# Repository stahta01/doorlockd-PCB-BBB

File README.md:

# doorlockd-PCB-BBB

Kicad drawing for doorlockd electronics on a Beagleboard black cape.

### component list
|Ref| |Value|
| --- | --- | --- |
|C1|C|1uF |
|C2|C|1uF|
|C3|CP|470u|
|D1|LED|LED|
|D2|1N4007|1N4007|
|D3|LED|LED|
|D4|1N4007|1N4007|
|J1|Conn_01x02|LED 1|
|J10|Conn_01x03|Duo LED|
|J11|Barrel_Jack_Switch|Barrel_Jack_Switch|
|J12|Conn_01x08|RFID RC522|
|J13|Conn_01x02|Solenoid 12V|
|J14|Conn_01x02|jumper|
|J2|Conn_01x02|Button 2|
|J3|Conn_01x02|LED 2|
|J4|Conn_01x02|Button 1|
|J5|Conn_01x02|Buzzer 12V|
|P8|Conn_02x23_Odd_Even|BeagleBone_Black_Header|
|P9|Conn_02x23_Odd_Even|BeagleBone_Black_Header|
|Q1|Q_NMOS_GDS|STU60N3LH5|
|Q2|Q_NMOS_GDS|STU60N3LH5|
|R1|R|Ω LED1 |
|R14|R|Ω DuoLED|
|R15|R|Ω DuoLED|
|R16|R|100|
|R17|R|2k2|
|R2|R|pull_up|
|R3|R|220|
|R4|R|Ω LED2|
|R5|R|pull_up|
|R6|R|220|
|R7|R|100|
|R8|R|2k2|
|U1|TSR_1-2450|TSR_1-2450|

#### LED resistor notes
Choose the resistors based on the LEDs you use.

|Led |resistors|
| --- | ---: |
|red | 100 ohm|
|green | 60 ohm|
|yellow | 48 ohm|
|blue |4 ohm|

### connected IO ports
| |port|chip,line<sup>\*1</sup>|name|
| --- | --- | --- | --- |
|IO|P8_17|gpiochip0 27|Button1|
|IO|P9_12|gpiochip1 28|Solenoid|
|IO|P9_14|gpiochip1 18|UILED1|
|IO|P8_18|gpiochip2 1|Button2|
|IO|P9_17|gpiochip0 5|RC522_SDA|
|IO|P9_22|gpiochip0 2|RC522_SCK|
|IO|P9_18|gpiochip0 4|RC522_MOSI|
|IO|P9_21|gpiochip0 3|RC522_MISO|
|IO|P9_15|gpiochip1 16|RC522_IRQ|
|IO|P9_23|gpiochip1 17|RC522_RST|
|IO|P8_13|gpiochip0 23|UI_DuoLED1r|
|IO|P8_19|gpiochip0 22|UI_DuoLED1g|
|IO|P9_16|gpiochip1 19|UILED2|
|IO|P8_9|gpiochip2 5|Buzzer|

<sub>*\*1):* GPIO Chip+line for gpiod, reference taken from https://elinux.org/Beagleboard:BeagleBone_cape_interface_spec </sub>

### Connecting PN532 board
This board was originally designed for use with the RC522 NFC reader,
but is also usable with the PN532 reader (which has better range and
reliability).

 - BBB SCK pin (`RC522_SCK`) is `UART2_RXD` -> connect to PN532 TX
 - BBB MISO pin (`RC522_MISO`) is `UART2_TXD` -> connect to PN532 RX
 - 5V can be taken from P9 pin 7 and/or 8 (needs extra pin soldered on)

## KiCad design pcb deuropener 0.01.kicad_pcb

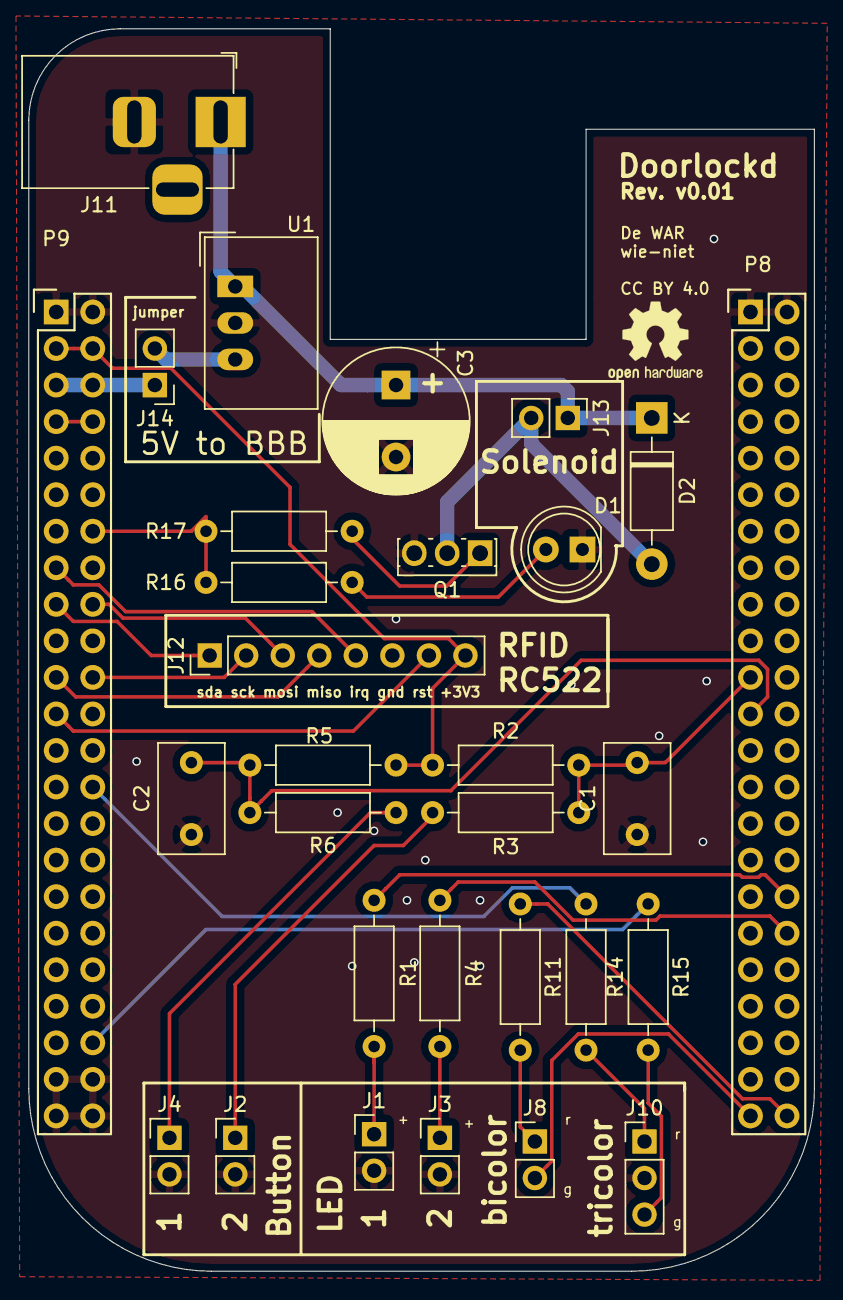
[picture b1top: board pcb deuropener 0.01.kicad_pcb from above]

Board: 2 copper layers, 54.6 x 86.4 mm, 30 parts (0 on the bottom side), 31 nets.

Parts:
C1, C2: C; C_Disc_D7.5mm_W4.4mm_P5.00mm
C3: 470u; CP_Radial_D10.0mm_P5.00mm
D1: LED; LED_D5.0mm
D2: 1N4007; D_DO-41_SOD81_P10.16mm_Horizontal
J1, J2, J3, J4, J8, J13, J14: Conn_01x02; PinHeader_1x02_P2.54mm_Vertical
J10: Conn_01x03; PinHeader_1x03_P2.54mm_Vertical
J11: Barrel_Jack_Switch; BarrelJack_Horizontal
J12: Conn_01x08; PinHeader_1x08_P2.54mm_Vertical
P8, P9: BeagleBone_Black_Header; Socket_BeagleBone_Black
Q1: STU60N3LH5; SIPAK_Vertical
R1, R2, R3, R4, R5, R6, R11, R14, R15, R16, R17: R; R_Axial_DIN0207_L6.3mm_D2.5mm_P10.16mm_Horizontal
U1: TSR_1-2450; Converter_DCDC_TRACO_TSR-1_THT

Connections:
+3V3: J12.8, P9.3, P9.4, R2.1, R5.1
+5V: J14.1, P9.5, P9.6
+12V: C3.1, D2.1, J11.1, J13.1, U1.1
Earth: C1.1, C2.1, C3.2, D1.1, J1.2, J2.2, J3.2, J4.2, J10.2, J11.2, J12.6, P8.1, P8.2, P9.1, P9.2, P9.43, P9.44, P9.45, P9.46, Q1.3, U1.2
IO-P8_21-Button2: C1.2, P8.21, R2.2, R3.1
IO-P8_23-Button1: C2.2, P8.23, R5.2, R6.1
IO-P8_34-UILED1: P8.34, R1.1
IO-P8_36-UILED2: P8.36, R4.1
IO-P8_45-UI_BiLED1g: J8.2, P8.45
IO-P8_46-UI_BiLED1r: P8.46, R11.1
IO-P9_14-Solenoid: P9.14, R16.1, R17.1
IO-P9_15-RC522_IRQ: J12.5, P9.15
IO-P9_17-RC522_SDA: J12.1, P9.17
IO-P9_18-RC522_MOSI: J12.3, P9.18
IO-P9_21-RC522_MISO: J12.4, P9.21
IO-P9_22-RC522_SCK: J12.2, P9.22
IO-P9_23-RC522_RST: J12.7, P9.23
IO-P9_28-UI_TriLED1r: P9.28, R14.2
IO-P9_42-UI_TriLED1g: P9.42, R15.2
unnamed: D1.2, R16.2
unnamed: D2.2, J13.2, Q1.2
unnamed: J1.1, R1.2
unnamed: J2.1, R3.2
unnamed: J3.1, R4.2
unnamed: J4.1, R6.2
unnamed: J8.1, R11.2
unnamed: J10.1, R14.1
unnamed: J10.3, R15.1
unnamed: J14.2, U1.3
unnamed: Q1.1, R17.2
SYS_5V: P9.7, P9.8

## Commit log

2019-05-21 First prototype rev v0.01
2019-05-21 Component list
2019-06-11 Fixed: 12V barreljack connected to wrong pin #1
2019-06-11 OSHW Logo was removec after last change, re-added (Place >> Footprint >> "search OSHW" and place the smalles logo on print).
2019-07-16 A lot of changes to rev 0.02
2019-07-16 A lot of changes for rev0.02 and fix for issue #2
2019-07-30 Better Earth track to FETs and Capacitor
2019-07-30 improved Earth path and 12V path to the southern area of the pcb.
2019-08-13 Documentation file added with GPIO port information and component list with values. in info_rev0.01.txt
2019-08-13 Rev 0.02
2019-08-13 resistor values per LED color
2019-08-29 updated component list
2019-08-29 IO ports and Component info updated for rev0.02
2019-09-10 fixed mix up of printed names "Solenoid" and "Buzzer". nothing changed to electronics #3
2019-09-10 Bug #3
2019-09-10 rev0.02.1
2019-09-10 rev0.02.1 issue #3
2019-09-17 Archive of rev0.01 including preview images of pcb and schematics
2019-09-17 Rename info_rev0.01.txt to info_rev0.01.md
2019-09-17 moved doorlockd-PCB-BBB rev0.01 into archive folder
2019-09-17 fixed markdown for info_rev0.01.md
2019-09-17 preview rev0.01 added
2019-09-17 Rename info_rev0.01.md to README.md
2021-03-05 add schematic
2021-03-05 add schematic preview
2021-11-04 added GPIO chip+line reference
    added GPIO chip+line reference
2021-11-04 add GPIO Chip+line for gpiod
    + some markup changes
2022-05-09 Remove a lot of parts and traces
2022-05-09 convert to kicad 6
2025-03-06 Document how to connect PN532 module

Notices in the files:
pcb deuropener 0.01.kicad_pcb:
CC BY 4.0
